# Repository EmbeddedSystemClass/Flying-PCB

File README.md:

# Infineon's full system solution for multicopter

Multicopter project by Management Center Innsbruck and Infineon Technologies Austria AG.

The here present project deals with the development of a radio-controlled quadcopter and focusses on two major topics:

- Design and implementation of an appropriate digital attitude controller/flightcontroller (named LARIX Flight Controller)
- Development of a brushless DC (BLDC) motor controller (named PINUS Electronic Speed Controller)

More information Infineon and Multicopters: http://www.infineon.com/multicopter

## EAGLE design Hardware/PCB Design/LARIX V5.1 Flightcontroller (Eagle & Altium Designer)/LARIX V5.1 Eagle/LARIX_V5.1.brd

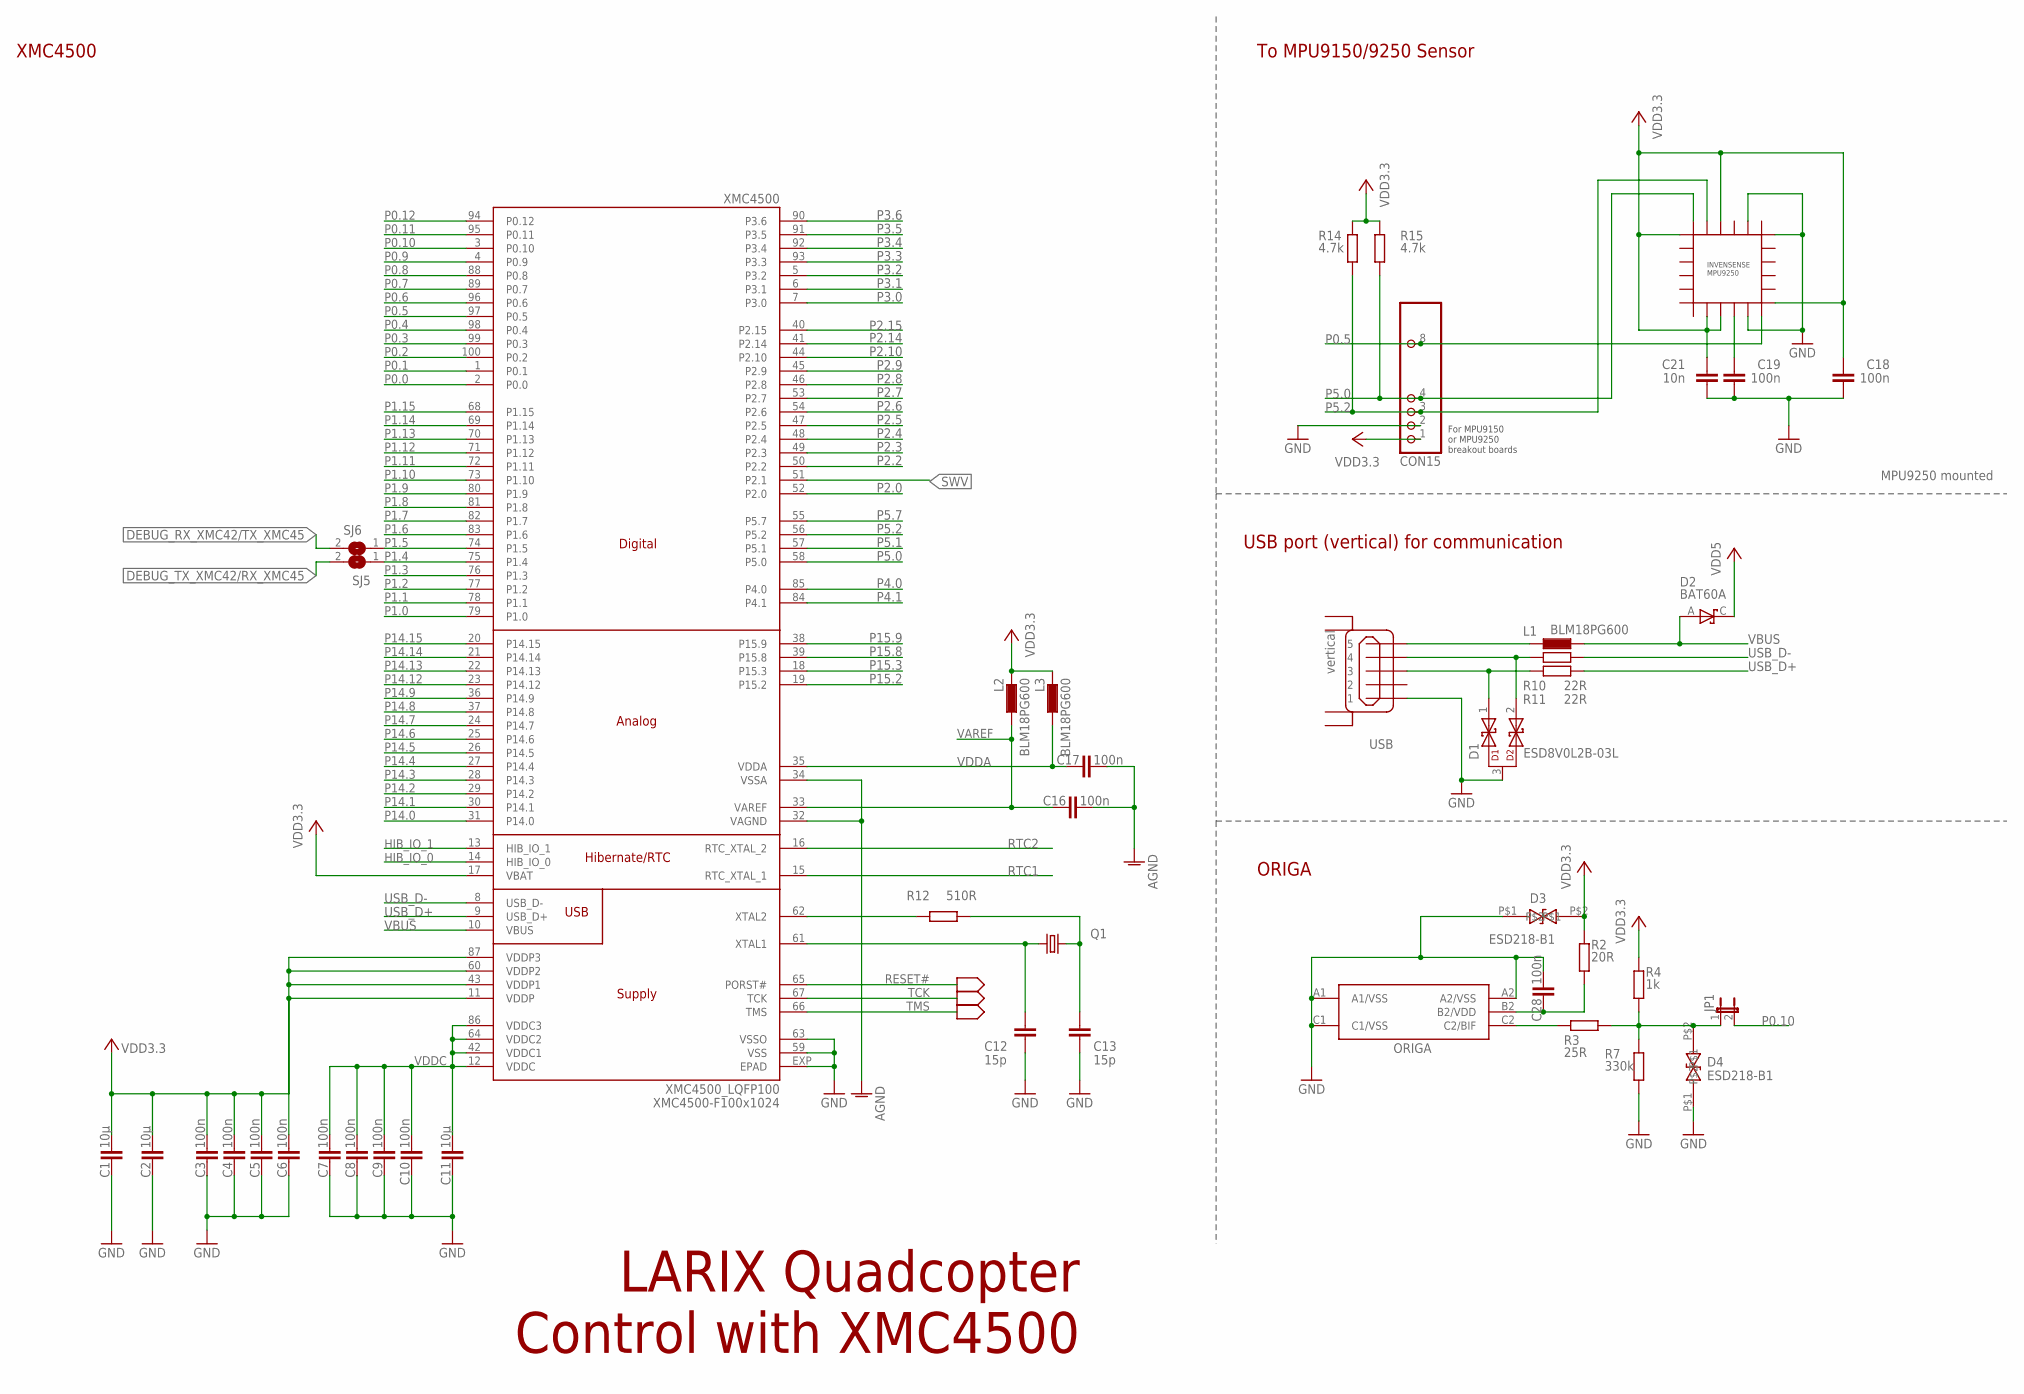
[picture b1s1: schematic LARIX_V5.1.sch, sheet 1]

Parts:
C1, C2, C11: 10µ; C0805K
C3, C4, C5, C6, C7, C8, C9, C10, C16, C17, C18, C19, C28: 100n; C0603
C12, C13: 15p; C0603
C21: 10n; C0603
CON15: PINHD-1X10; 1X10
D1: ESD8V0L2B-03L; TSLP-3-1
D2: BAT60A; SOD323-R
D3, D4: ESD218-B1-02EL; TSLP-2-20
JP1: JP1E; JP1
L1, L2, L3: BLM18PG600; L1608
MPU9250: MPU9250; QFN3X3-24+
ORIGA: ORIGA2L; WLB-5
Q1: 12MHZ/S/3.2X2.5; 32X25_4PAD
R2: 20R; R0603
R3: 25R; R0603
R4: 1k; R0603
R7: 330k; R0603
R10, R11: 22R; R0603
R12: 510R; R0603
R14, R15: 4.7k; R0603
SJ5, SJ6: SJ
USB: vertical; USBVERTICAL
XMC4500: XMC4500_LQFP100; P/PG-LQFP-100-11

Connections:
AGND: C16.2, C17.2, XMC4500.32 (VAGND), XMC4500.34 (VSSA)
DEBUG_RX_XMC42/TX_XMC45: SJ6.2; also elsewhere on the board
DEBUG_TX_XMC42/RX_XMC45: SJ5.2; also elsewhere on the board
GND: C1.2, C2.2, C3.2, C4.2, C5.2, C6.2, C7.2, C8.2, C9.2, C10.2, C11.2, C12.2, C13.2, C18.1, C19.1, C21.1, C28.1, CON15.2, D1.3, D3.P$1, D4.P$1, MPU9250.11, MPU9250.18, MPU9250.20, ORIGA.A1 (A1/VSS), ORIGA.A2 (A2/VSS), ORIGA.C1 (C1/VSS), R7.2, USB.1, XMC4500.59 (VSS), XMC4500.63 (VSSO), XMC4500.EXP (EPAD); also elsewhere on the board
HIB_IO_0: XMC4500.14 (HIB_IO_0)
HIB_IO_1: XMC4500.13 (HIB_IO_1)
unnamed: C28.2, ORIGA.B2 (B2/VDD), R2.2
unnamed: R12.1, XMC4500.62 (XTAL2)
unnamed: C13.1, Q1.3 (2), R12.2
unnamed: C12.1, Q1.1, XMC4500.61 (XTAL1)
unnamed: D4.P$2, JP1.1, R3.2, R4.2, R7.1
unnamed: L1.2, USB.5
unnamed: ORIGA.C2 (C2/BIF), R3.1
unnamed: D1.2, R10.1, USB.4
unnamed: C19.2, MPU9250.10
unnamed: D1.1, R11.1, USB.3+ (3)
P0.0: XMC4500.2 (P0.0); also elsewhere on the board
P0.1: XMC4500.1 (P0.1); also elsewhere on the board
P0.2: XMC4500.100 (P0.2); also elsewhere on the board
P0.3: XMC4500.99 (P0.3); also elsewhere on the board
P0.4: XMC4500.98 (P0.4); also elsewhere on the board
P0.5: CON15.8, MPU9250.12, XMC4500.97 (P0.5)
P0.6: XMC4500.96 (P0.6)
P0.7: XMC4500.89 (P0.7); also elsewhere on the board
P0.8: XMC4500.88 (P0.8)
P0.9: XMC4500.4 (P0.9); also elsewhere on the board
P0.10: JP1.2, XMC4500.3 (P0.10)
P0.11: XMC4500.95 (P0.11)
P0.12: XMC4500.94 (P0.12)
P1.0: XMC4500.79 (P1.0); also elsewhere on the board
P1.1: XMC4500.78 (P1.1); also elsewhere on the board
P1.2: XMC4500.77 (P1.2); also elsewhere on the board
P1.3: XMC4500.76 (P1.3); also elsewhere on the board
P1.4: SJ5.1, XMC4500.75 (P1.4)
P1.5: SJ6.1, XMC4500.74 (P1.5); also elsewhere on the board
P1.6: XMC4500.83 (P1.6)
P1.7: XMC4500.82 (P1.7)
P1.8: XMC4500.81 (P1.8)
P1.9: XMC4500.80 (P1.9)
P1.10: XMC4500.73 (P1.10)
P1.11: XMC4500.72 (P1.11)
P1.12: XMC4500.71 (P1.12)
P1.13: XMC4500.70 (P1.13)
P1.14: XMC4500.69 (P1.14)
P1.15: XMC4500.68 (P1.15); also elsewhere on the board
P2.0: XMC4500.52 (P2.0)
P2.2: XMC4500.50 (P2.2); also elsewhere on the board
P2.3: XMC4500.49 (P2.3); also elsewhere on the board
P2.4: XMC4500.48 (P2.4); also elsewhere on the board
P2.5: XMC4500.47 (P2.5); also elsewhere on the board
P2.6: XMC4500.54 (P2.6)
P2.7: XMC4500.53 (P2.7)
P2.8: XMC4500.46 (P2.8)
P2.9: XMC4500.45 (P2.9)
P2.10: XMC4500.44 (P2.10)
P2.14: XMC4500.41 (P2.14)
P2.15: XMC4500.40 (P2.15)
P3.0: XMC4500.7 (P3.0); also elsewhere on the board
P3.1: XMC4500.6 (P3.1); also elsewhere on the board
P3.2: XMC4500.5 (P3.2); also elsewhere on the board
P3.3: XMC4500.93 (P3.3)
P3.4: XMC4500.92 (P3.4)
P3.5: XMC4500.91 (P3.5); also elsewhere on the board
P3.6: XMC4500.90 (P3.6)
P4.0: XMC4500.85 (P4.0); also elsewhere on the board
P4.1: XMC4500.84 (P4.1)
P5.0: CON15.4, MPU9250.24, R15.1, XMC4500.58 (P5.0)
P5.1: XMC4500.57 (P5.1); also elsewhere on the board
P5.2: CON15.3, MPU9250.23, R14.1, XMC4500.56 (P5.2)
P5.7: XMC4500.55 (P5.7)
P14.0: XMC4500.31 (P14.0)
P14.1: XMC4500.30 (P14.1)
P14.2: XMC4500.29 (P14.2)
P14.3: XMC4500.28 (P14.3)
P14.4: XMC4500.27 (P14.4)
P14.5: XMC4500.26 (P14.5); also elsewhere on the board
P14.6: XMC4500.25 (P14.6)
P14.7: XMC4500.24 (P14.7); also elsewhere on the board
P14.8: XMC4500.37 (P14.8); also elsewhere on the board
P14.9: XMC4500.36 (P14.9)
P14.12: XMC4500.23 (P14.12)
P14.13: XMC4500.22 (P14.13)
P14.14: XMC4500.21 (P14.14)
P14.15: XMC4500.20 (P14.15)
P15.2: XMC4500.19 (P15.2)
P15.3: XMC4500.18 (P15.3)
P15.8: XMC4500.39 (P15.8)
P15.9: XMC4500.38 (P15.9)
RESET#: XMC4500.65 (PORST#); also elsewhere on the board
RTC1: XMC4500.15 (RTC_XTAL_1)
RTC2: XMC4500.16 (RTC_XTAL_2)
SWV: XMC4500.51 (P2.1); also elsewhere on the board
TCK: XMC4500.67 (TCK); also elsewhere on the board
TMS: XMC4500.66 (TMS); also elsewhere on the board
USB_D+: R11.2, XMC4500.9 (USB_D+)
USB_D-: R10.2, XMC4500.8 (USB_D-)
VAREF: C16.1, L2.1, XMC4500.33 (VAREF)
VBUS: D2.A, L1.1, XMC4500.10 (VBUS)
VDD3.3: C1.1, C2.1, C3.1, C4.1, C5.1, C6.1, C18.2, C21.2, CON15.1, D3.P$2, L2.2, L3.2, MPU9250.1, MPU9250.8, MPU9250.9, MPU9250.13, MPU9250.22, R2.1, R4.1, R14.2, R15.2, XMC4500.11 (VDDP), XMC4500.17 (VBAT), XMC4500.43 (VDDP1), XMC4500.60 (VDDP2), XMC4500.87 (VDDP3); also elsewhere on the board
VDD5: D2.C; also elsewhere on the board
VDDA: C17.1, L3.1, XMC4500.35 (VDDA)
VDDC: C7.1, C8.1, C9.1, C10.1, C11.1, XMC4500.12 (VDDC), XMC4500.42 (VDDC1), XMC4500.64 (VDDC2), XMC4500.86 (VDDC3)

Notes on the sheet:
LARIX Quadcopter Control with XMC4500
XMC4500-F100x1024
To MPU9150/9250 Sensor
ORIGA
XMC4500
For MPU9150 or MPU9250 breakout boards
USB port (vertical) for communication
ESD218-B1
MPU9250 mounted

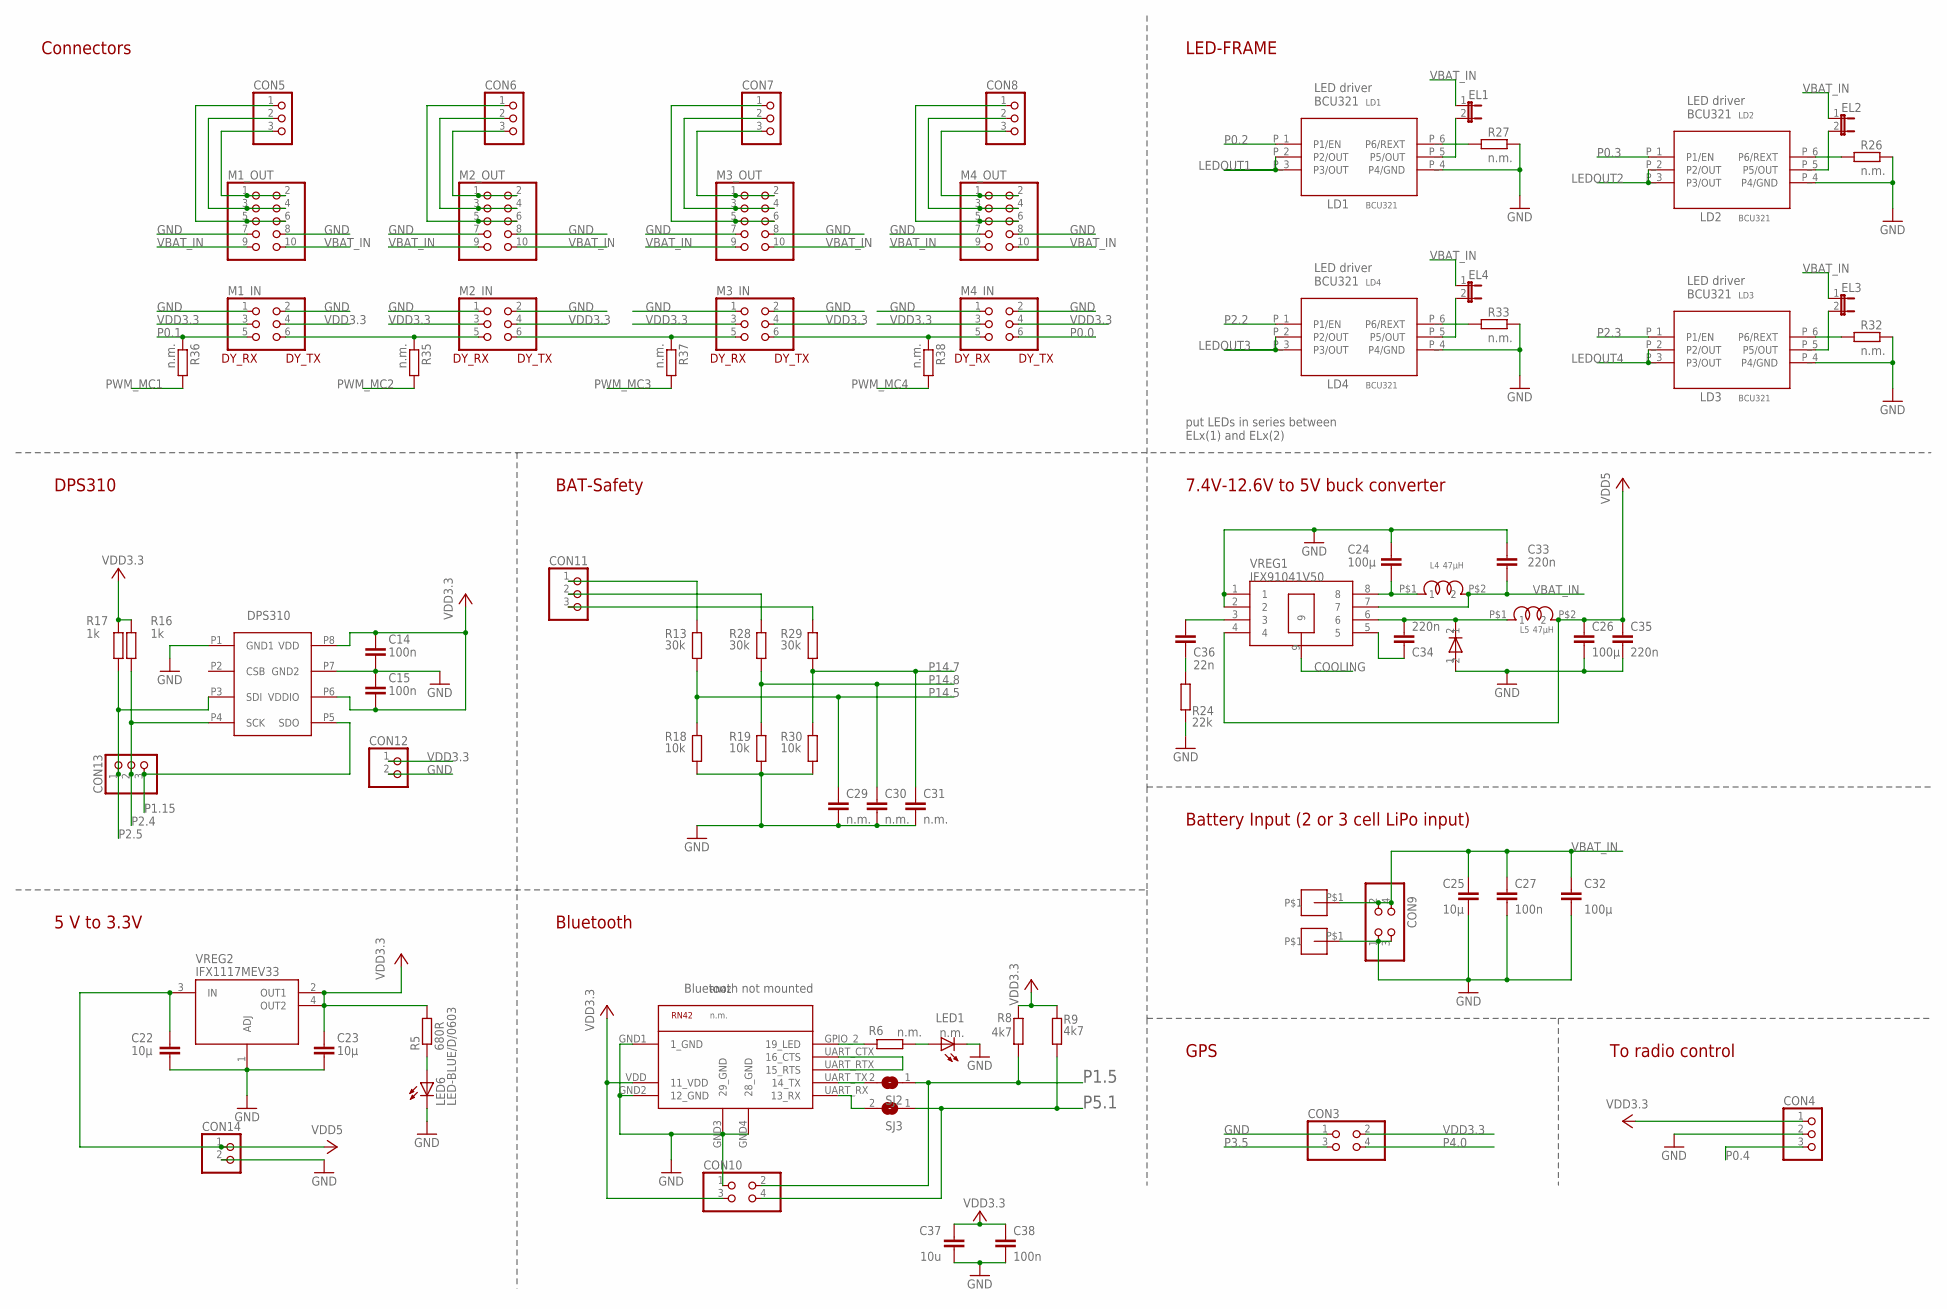
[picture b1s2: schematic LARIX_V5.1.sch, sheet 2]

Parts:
C14, C15, C27, C38: 100n; C0603
C22, C23, C25: 10µ; C0805K
C24, C26, C32: 100µ; C1210
C29, C30, C31: n.m.; C0603
C33, C34, C35: 220n; C0603
C36: 22n; C0603
C37: 10u; C0805K
CON3, CON9, CON10: PINHD-2X2; 2X02
CON4, CON5, CON6, CON7, CON8, CON11, CON13: PINHD-1X3; 1X03
CON12, CON14: PINHD-1X2; 1X02
D6: BAS21-03W; INF-SOD323_V_1PRIMARY
DPS310: Infineon; LGA8R125P0X4_500X300X120
EL1, EL2, EL3, EL4: JP1E; JP1
L4, L5: 47µH; WE-TPC
LD1, LD2, LD3, LD4: BCU321; SC74
LED1: n.m.; CHIPLED_0603
LED6: LED-BLUE/D/0603; CHIPLED_0603
M1_IN, M2_IN, M3_IN, M4_IN: PINHD-2X3; 2X03
M1_OUT, M2_OUT, M3_OUT, M4_OUT: PINHD-2X5; 2X05
PAD1, PAD2: PAD-BATTERY; BATT-SOLDER
R5: 680R; R0603
R6, R26, R27, R32, R33, R35, R36, R37, R38: n.m.; R0603
R8, R9: 4k7; R0603
R13, R28, R29: 30k; R0603
R16, R17: 1k; R0603
R18, R19, R30: 10k; R0603
R24: 22k; R0603
RN42: n.m.; RN42+SHIELD
SJ2, SJ3: SJ
VREG1: IFX91041V50; INF-PG-DSO-8-27_N_1PRIMARY
VREG2: IFX1117MEV33; SOT223

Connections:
COOLING: VREG1.9
GND: C14.2, C15.1, C22.2, C23.2, C24.1, C25.2, C26.2, C27.2, C29.2, C30.2, C31.2, C32.2, C33.1, C35.2, C37.2, C38.2, CON3.1, CON4.2, CON9.1, CON9.3, CON10.1, CON12.2, CON14.2, D6.1, DPS310.P1 (GND1), DPS310.P7 (GND2), LD1.P_4 (P4/GND), LD2.P_4 (P4/GND), LD3.P_4 (P4/GND), LD4.P_4 (P4/GND), LED1.C, LED6.C, M1_IN.1, M1_IN.2, M1_OUT.7, M1_OUT.8, M2_IN.1, M2_IN.2, M2_OUT.7, M2_OUT.8, M3_IN.1, M3_IN.2, M3_OUT.7, M3_OUT.8, M4_IN.1, M4_IN.2, M4_OUT.7, M4_OUT.8, PAD2.P$1, R18.2, R19.2, R24.2, R26.2, R27.2, R30.2, R32.2, R33.2, RN42.GND1 (1_GND), RN42.GND2 (12_GND), RN42.GND3 (29_GND), RN42.GND4 (28_GND), VREG1.1, VREG1.2, VREG2.1 (ADJ); also elsewhere on the board
LEDOUT1: EL1.2, LD1.P_2 (P2/OUT), LD1.P_3 (P3/OUT), LD1.P_5 (P5/OUT)
LEDOUT2: EL2.2, LD2.P_2 (P2/OUT), LD2.P_3 (P3/OUT), LD2.P_5 (P5/OUT)
LEDOUT3: EL4.2, LD4.P_2 (P2/OUT), LD4.P_3 (P3/OUT), LD4.P_5 (P5/OUT)
LEDOUT4: EL3.2, LD3.P_2 (P2/OUT), LD3.P_3 (P3/OUT), LD3.P_5 (P5/OUT)
unnamed: C36.1, VREG1.3
unnamed: CON5.1, M1_OUT.5, M1_OUT.6
unnamed: LED6.A, R5.1
unnamed: M2_IN.6, M3_IN.5, R37.1
unnamed: C36.2, R24.1
unnamed: LED1.A, R6.1
unnamed: CON5.2, M1_OUT.3, M1_OUT.4
unnamed: CON5.3, M1_OUT.1, M1_OUT.2
unnamed: R6.2, RN42.GPIO_2 (19_LED)
unnamed: RN42.UART_CTX (16_CTS), RN42.UART_RTX (15_RTS)
unnamed: C24.2, L4.P$1 (1), VREG1.8
unnamed: C34.1, D6.2, L5.P$1 (1), VREG1.6
unnamed: LD2.P_6 (P6/REXT), R26.1
unnamed: LD1.P_6 (P6/REXT), R27.1
unnamed: CON6.1, M2_OUT.5, M2_OUT.6
unnamed: CON11.1, R13.1
unnamed: CON6.3, M2_OUT.1, M2_OUT.2
unnamed: CON6.2, M2_OUT.3, M2_OUT.4
unnamed: CON11.2, R28.1
unnamed: CON8.1, M4_OUT.5, M4_OUT.6
unnamed: CON11.3, R29.1
unnamed: CON8.3, M4_OUT.1, M4_OUT.2
unnamed: CON8.2, M4_OUT.3, M4_OUT.4
unnamed: C34.2, VREG1.5
unnamed: CON7.1, M3_OUT.5, M3_OUT.6
unnamed: CON7.2, M3_OUT.3, M3_OUT.4
unnamed: CON7.3, M3_OUT.1, M3_OUT.2
unnamed: M3_IN.6, M4_IN.5, R38.1
unnamed: M1_IN.6, M2_IN.5, R35.1
unnamed: LD3.P_6 (P6/REXT), R32.1
unnamed: LD4.P_6 (P6/REXT), R33.1
unnamed: RN42.UART_TX (14_TX), SJ2.2
unnamed: RN42.UART_RX (13_RX), SJ3.2
P0.0: M4_IN.6; also elsewhere on the board
P0.1: M1_IN.5, R36.1; also elsewhere on the board
P0.2: LD1.P_1 (P1/EN); also elsewhere on the board
P0.3: LD2.P_1 (P1/EN); also elsewhere on the board
P0.4: CON4.3; also elsewhere on the board
P1.5: CON10.2, R8.2, SJ2.1; also elsewhere on the board
P1.15: CON13.3, DPS310.P5 (SDO); also elsewhere on the board
P2.2: LD4.P_1 (P1/EN); also elsewhere on the board
P2.3: LD3.P_1 (P1/EN); also elsewhere on the board
P2.4: CON13.2, DPS310.P4 (SCK), R16.2; also elsewhere on the board
P2.5: CON13.1, DPS310.P3 (SDI), R17.2; also elsewhere on the board
P3.5: CON3.3; also elsewhere on the board
P4.0: CON3.4; also elsewhere on the board
P5.1: CON10.4, R9.2, SJ3.1; also elsewhere on the board
P14.5: C29.1, R13.2, R18.1; also elsewhere on the board
P14.7: C31.1, R29.2, R30.1; also elsewhere on the board
P14.8: C30.1, R19.1, R28.2; also elsewhere on the board
PWM_MC1: R36.2; also elsewhere on the board
PWM_MC2: R35.2; also elsewhere on the board
PWM_MC3: R37.2; also elsewhere on the board
PWM_MC4: R38.2; also elsewhere on the board
VBAT_IN: C25.1, C27.1, C32.1, C33.2, CON9.2, CON9.4, EL1.1, EL2.1, EL3.1, EL4.1, L4.P$2 (2), M1_OUT.9, M1_OUT.10, M2_OUT.9, M2_OUT.10, M3_OUT.9, M3_OUT.10, M4_OUT.9, M4_OUT.10, PAD1.P$1, VREG1.7
VDD3.3: C14.1, C15.2, C23.1, C37.1, C38.1, CON3.2, CON4.1, CON10.3, CON12.1, DPS310.P6 (VDDIO), DPS310.P8 (VDD), M1_IN.3, M1_IN.4, M2_IN.3, M2_IN.4, M3_IN.3, M3_IN.4, M4_IN.3, M4_IN.4, R5.2, R8.1, R9.1, R16.1, R17.1, RN42.VDD (11_VDD), VREG2.2 (OUT1), VREG2.4 (OUT2); also elsewhere on the board
VDD5: C22.1, C26.1, C35.1, CON14.1, L5.P$2 (2), VREG1.4, VREG2.3 (IN); also elsewhere on the board

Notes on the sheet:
Connectors
DY_RX
DY_TX
LED-FRAME
LED driver BCU321
LD1
LD2
LD4
LD3
GPS
To radio control
DPS310
5 V to 3.3V
7.4V-12.6V to 5V buck converter
Bluetooth
BAT-Safety
Battery Input (2 or 3 cell LiPo input)
VREG1 IFX91041V50
Bluetooth not mounted
put LEDs in series between ELx(1) and ELx(2)

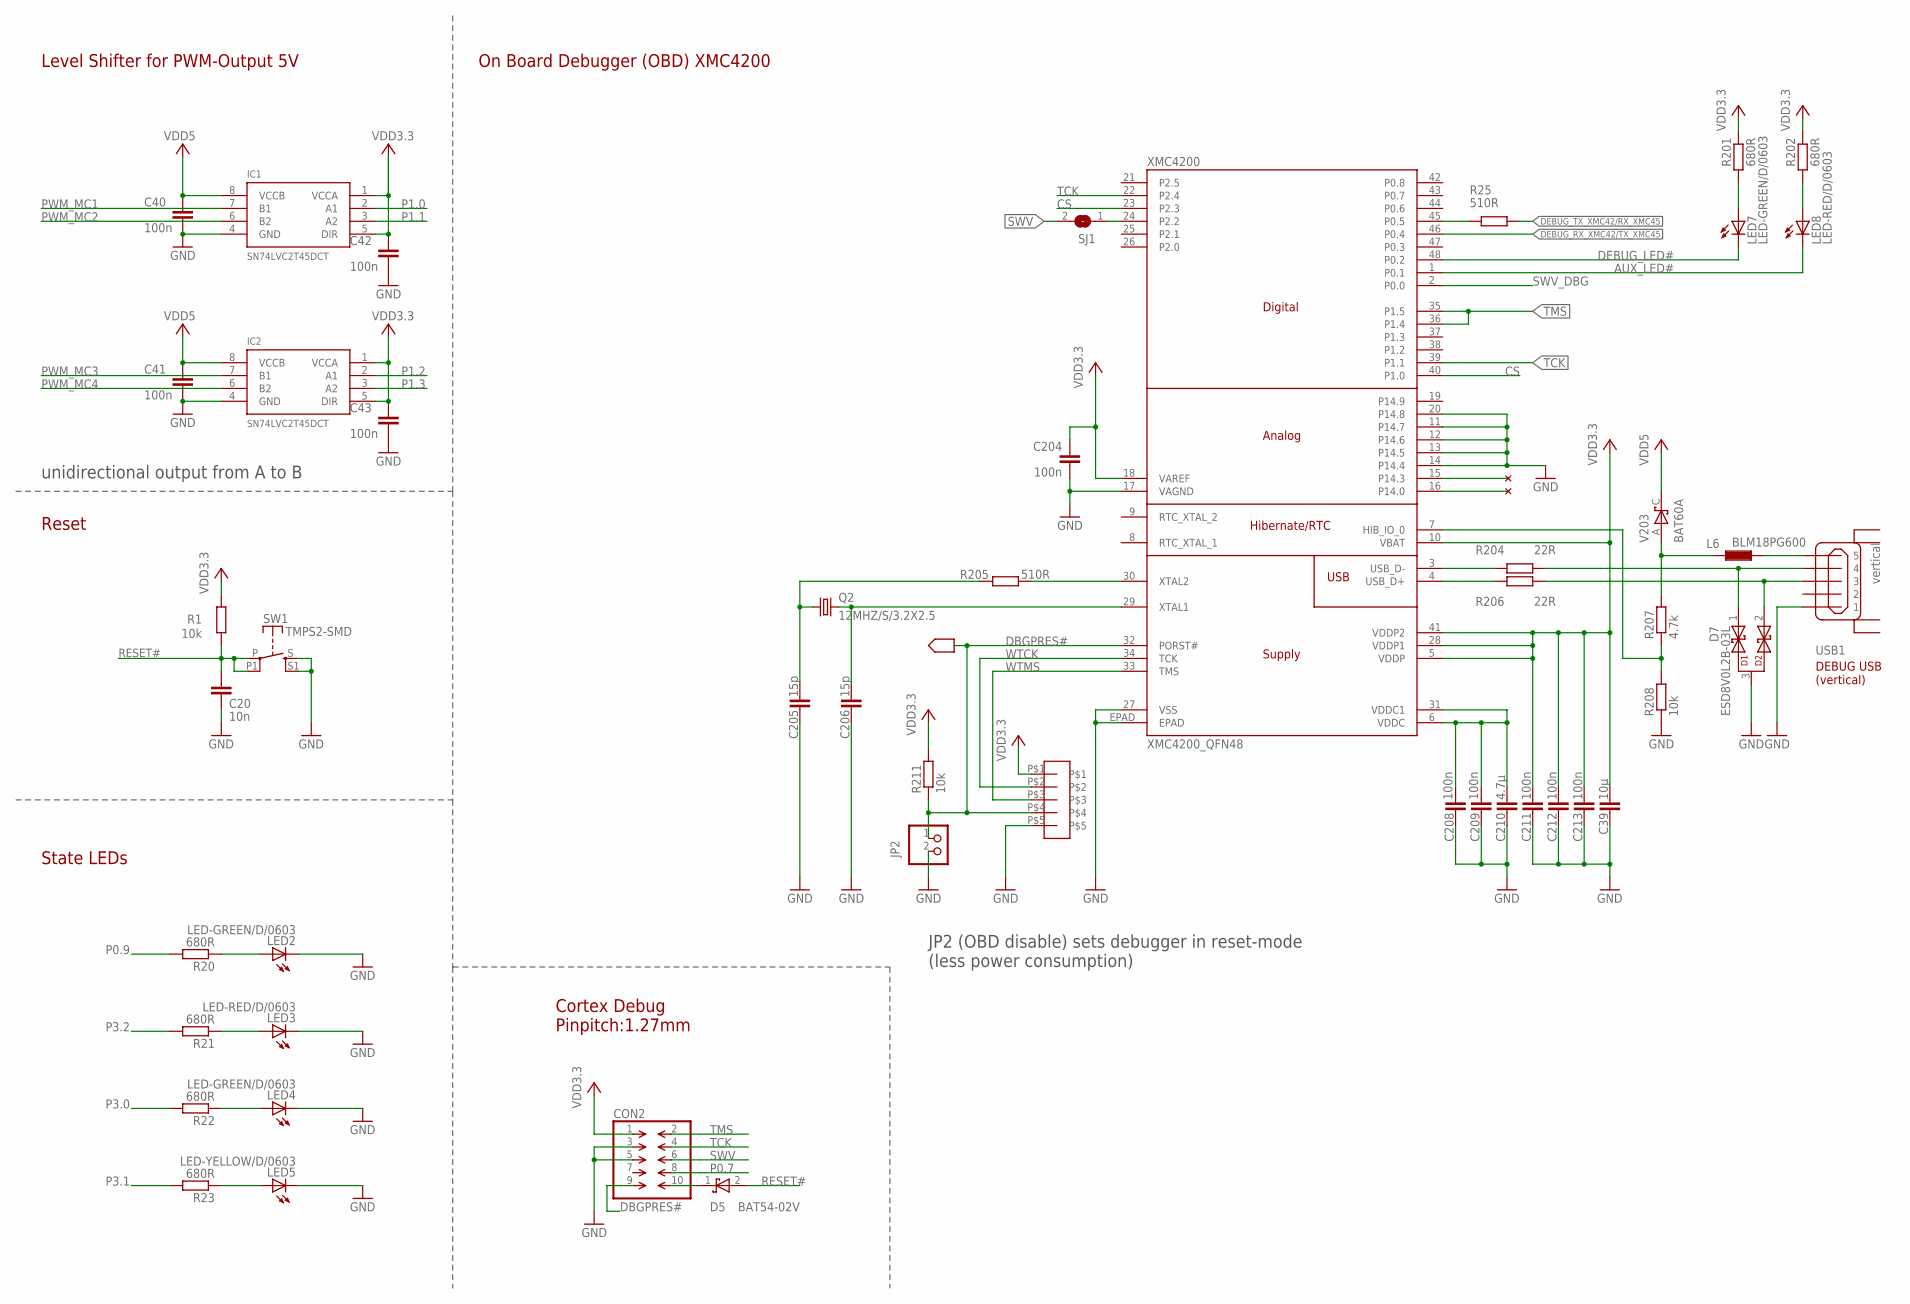
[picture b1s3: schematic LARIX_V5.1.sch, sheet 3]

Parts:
C20: 10n; C0603
C39: 10µ; C0805K
C40, C41, C42, C43: 100n; C0603
C204, C208, C209, C211, C212, C213: 100n; C0402
C205, C206: 15p; C0402
C210: 4.7µ; C0805K
CON2: FTSH-105-01-F-D-K
D5: BAT54-02V; SC79
D7: ESD8V0L2B-03L; TSLP-3-1
IC1, IC2: SN74LVC2T45DCT; DCT_R-PDSO-G8
JP2: PINHD-1X2; 1X02
L6: BLM18PG600; L1608
LED2, LED4, LED7: LED-GREEN/D/0603; CHIPLED_0603
LED3, LED8: LED-RED/D/0603; CHIPLED_0603
LED5: LED-YELLOW/D/0603; CHIPLED_0603
Q2: 12MHZ/S/3.2X2.5; 32X25_4PAD
R1: 10k; R0603
R20, R21, R22, R23, R201, R202: 680R; R0603
R25: 510R; R0402
R204, R206: 22R; R0402
R205: 510R; R0603
R207: 4.7k; R0402
R208, R211: 10k; R0402
SJ1: SJ
SW1: TMPS2-SMD; FSM2JSMA
U$9: 127MARKED; PINHEAD_127
U$11: SEGGER.L_100; LOGO_100
USB1: vertical; USBVERTICAL
V203: BAT60A; SOD323-R
XMC4200: XMC4200_QFN48; QFN-48-7X7

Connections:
AUX_LED#: LED8.C, XMC4200.1 (P0.1)
CS: XMC4200.23 (P2.3), XMC4200.40 (P1.0)
DBGPRES#: CON2.9, JP2.1, R211.1, U$9.P$4, XMC4200.32 (PORST#)
DEBUG_LED#: LED7.C, XMC4200.48 (P0.2)
DEBUG_RX_XMC42/TX_XMC45: XMC4200.46 (P0.4); also elsewhere on the board
DEBUG_TX_XMC42/RX_XMC45: R25.2; also elsewhere on the board
GND: C20.2, C39.2, C40.2, C41.2, C42.2, C43.2, C204.2, C205.2, C206.2, C208.2, C209.2, C210.2, C211.2, C212.2, C213.2, CON2.3, CON2.5, D7.3, IC1.4 (GND), IC2.4 (GND), JP2.2, LED2.C, LED3.C, LED4.C, LED5.C, R208.1, SW1.S, SW1.S1 (S), U$9.P$5, USB1.1, XMC4200.11 (P14.7), XMC4200.12 (P14.6), XMC4200.13 (P14.5), XMC4200.14 (P14.4), XMC4200.17 (VAGND), XMC4200.20 (P14.8), XMC4200.27 (VSS), XMC4200.EPAD; also elsewhere on the board
unnamed: LED2.A, R20.1
unnamed: LED3.A, R21.1
unnamed: D7.1, R204.2, USB1.4
unnamed: CON2.10, D5.1 (C)
unnamed: LED4.A, R22.1
unnamed: LED5.A, R23.1
unnamed: D7.2, R206.2, USB1.3+ (3)
unnamed: C205.1, Q2.1, R205.2
unnamed: R205.1, XMC4200.30 (XTAL2)
unnamed: L6.2, R207.2, V203.A
unnamed: C206.1, Q2.3 (2), XMC4200.29 (XTAL1)
unnamed: LED7.A, R201.2
unnamed: R25.1, XMC4200.45 (P0.5)
unnamed: R207.1, R208.2, XMC4200.7 (HIB_IO_0)
unnamed: LED8.A, R202.2
P0.7: CON2.8; also elsewhere on the board
P0.9: R20.2; also elsewhere on the board
P1.0: IC1.2 (A1); also elsewhere on the board
P1.1: IC1.3 (A2); also elsewhere on the board
P1.2: IC2.2 (A1); also elsewhere on the board
P1.3: IC2.3 (A2); also elsewhere on the board
P3.0: R22.2; also elsewhere on the board
P3.1: R23.2; also elsewhere on the board
P3.2: R21.2; also elsewhere on the board
PWM_MC1: IC1.7 (B1); also elsewhere on the board
PWM_MC2: IC1.6 (B2); also elsewhere on the board
PWM_MC3: IC2.7 (B1); also elsewhere on the board
PWM_MC4: IC2.6 (B2); also elsewhere on the board
RESET#: C20.1, D5.2 (A), R1.1, SW1.P, SW1.P1; also elsewhere on the board
SWV: CON2.6, SJ1.2; also elsewhere on the board
SWV_DBG: SJ1.1, XMC4200.2 (P0.0), XMC4200.24 (P2.2)
TCK: CON2.4, XMC4200.22 (P2.4), XMC4200.39 (P1.1); also elsewhere on the board
TMS: CON2.2, XMC4200.35 (P1.5), XMC4200.36 (P1.4); also elsewhere on the board
USBVCC: L6.1, USB1.5
VDD3.3: C39.1, C42.1, C43.1, C204.1, C211.1, C212.1, C213.1, CON2.1, IC1.1 (VCCA), IC1.5 (DIR), IC2.1 (VCCA), IC2.5 (DIR), R1.2, R201.1, R202.1, R211.2, U$9.P$1, XMC4200.5 (VDDP), XMC4200.10 (VBAT), XMC4200.18 (VAREF), XMC4200.28 (VDDP1), XMC4200.41 (VDDP2); also elsewhere on the board
VDD5: C40.1, C41.1, IC1.8 (VCCB), IC2.8 (VCCB), V203.C; also elsewhere on the board
WTCK: U$9.P$2, XMC4200.34 (TCK)
WTMS: U$9.P$3, XMC4200.33 (TMS)
WUSB_DM: R204.1, XMC4200.3 (USB_D-)
WUSB_DP: R206.1, XMC4200.4 (USB_D+)
WVDDC: C208.1, C209.1, C210.1, XMC4200.6 (VDDC), XMC4200.31 (VDDC1)

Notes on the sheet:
State LEDs
Reset
Level Shifter for PWM-Output 5V
DEBUG USB (vertical)
Cortex Debug Pinpitch:1.27mm
On Board Debugger (OBD) XMC4200
JP2 (OBD disable) sets debugger in reset-mode (less power consumption)
unidirectional output from A to B

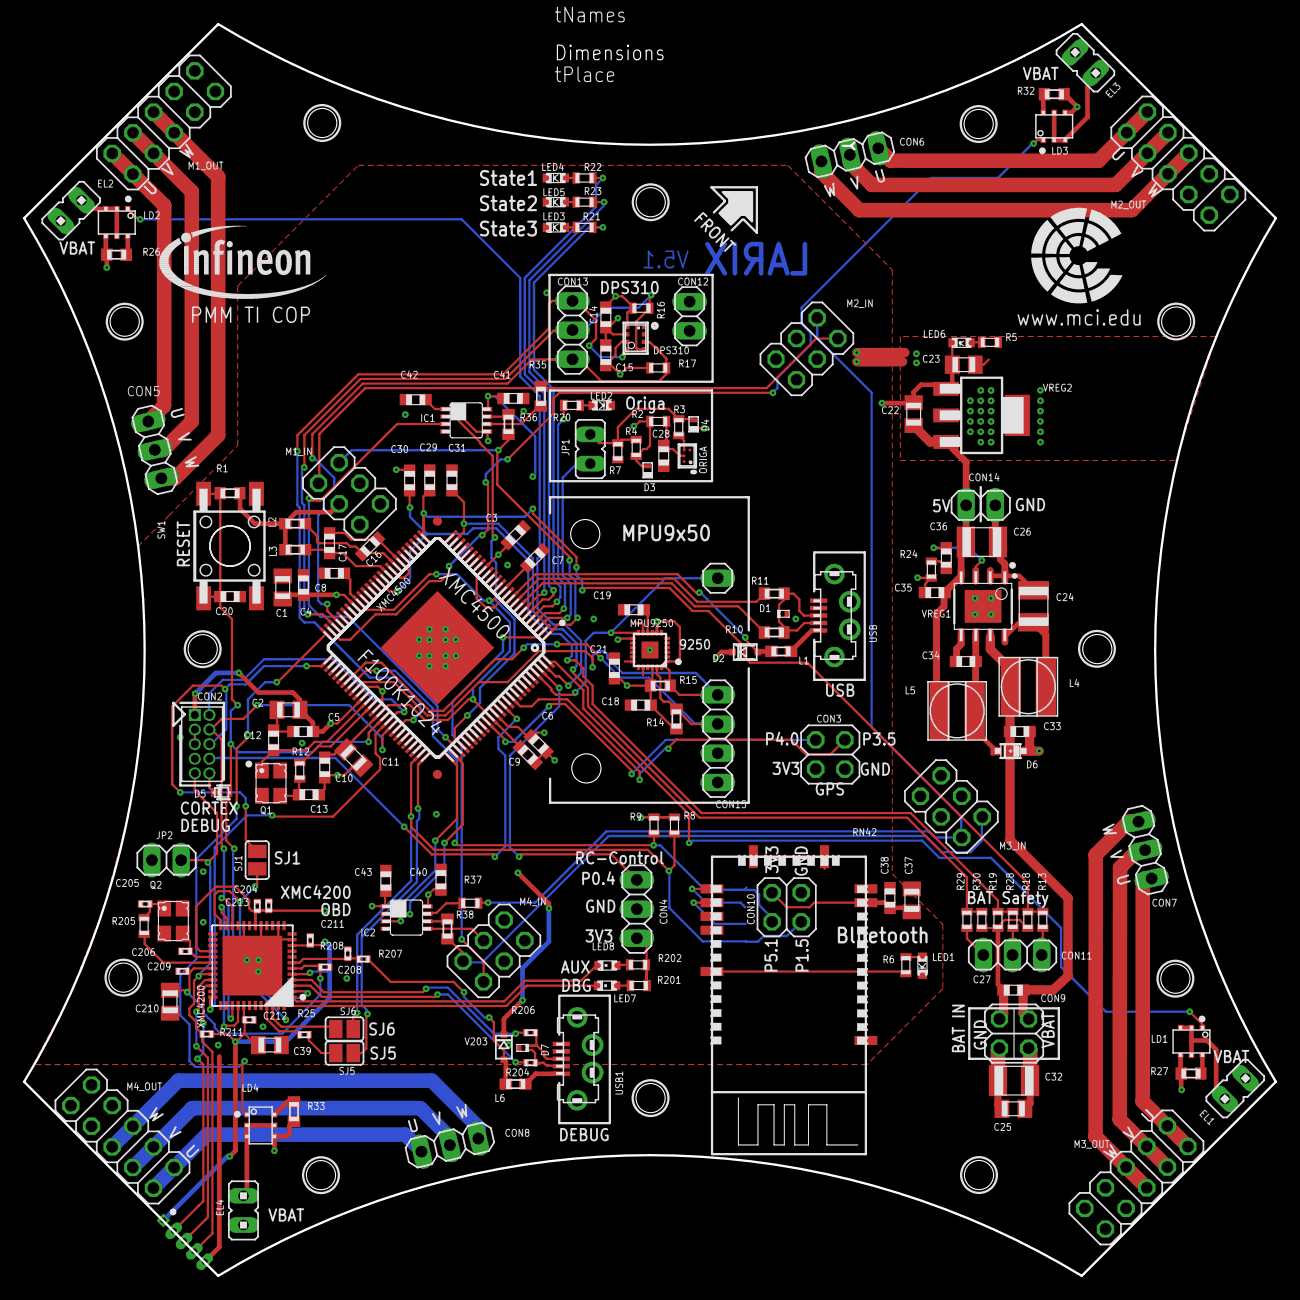
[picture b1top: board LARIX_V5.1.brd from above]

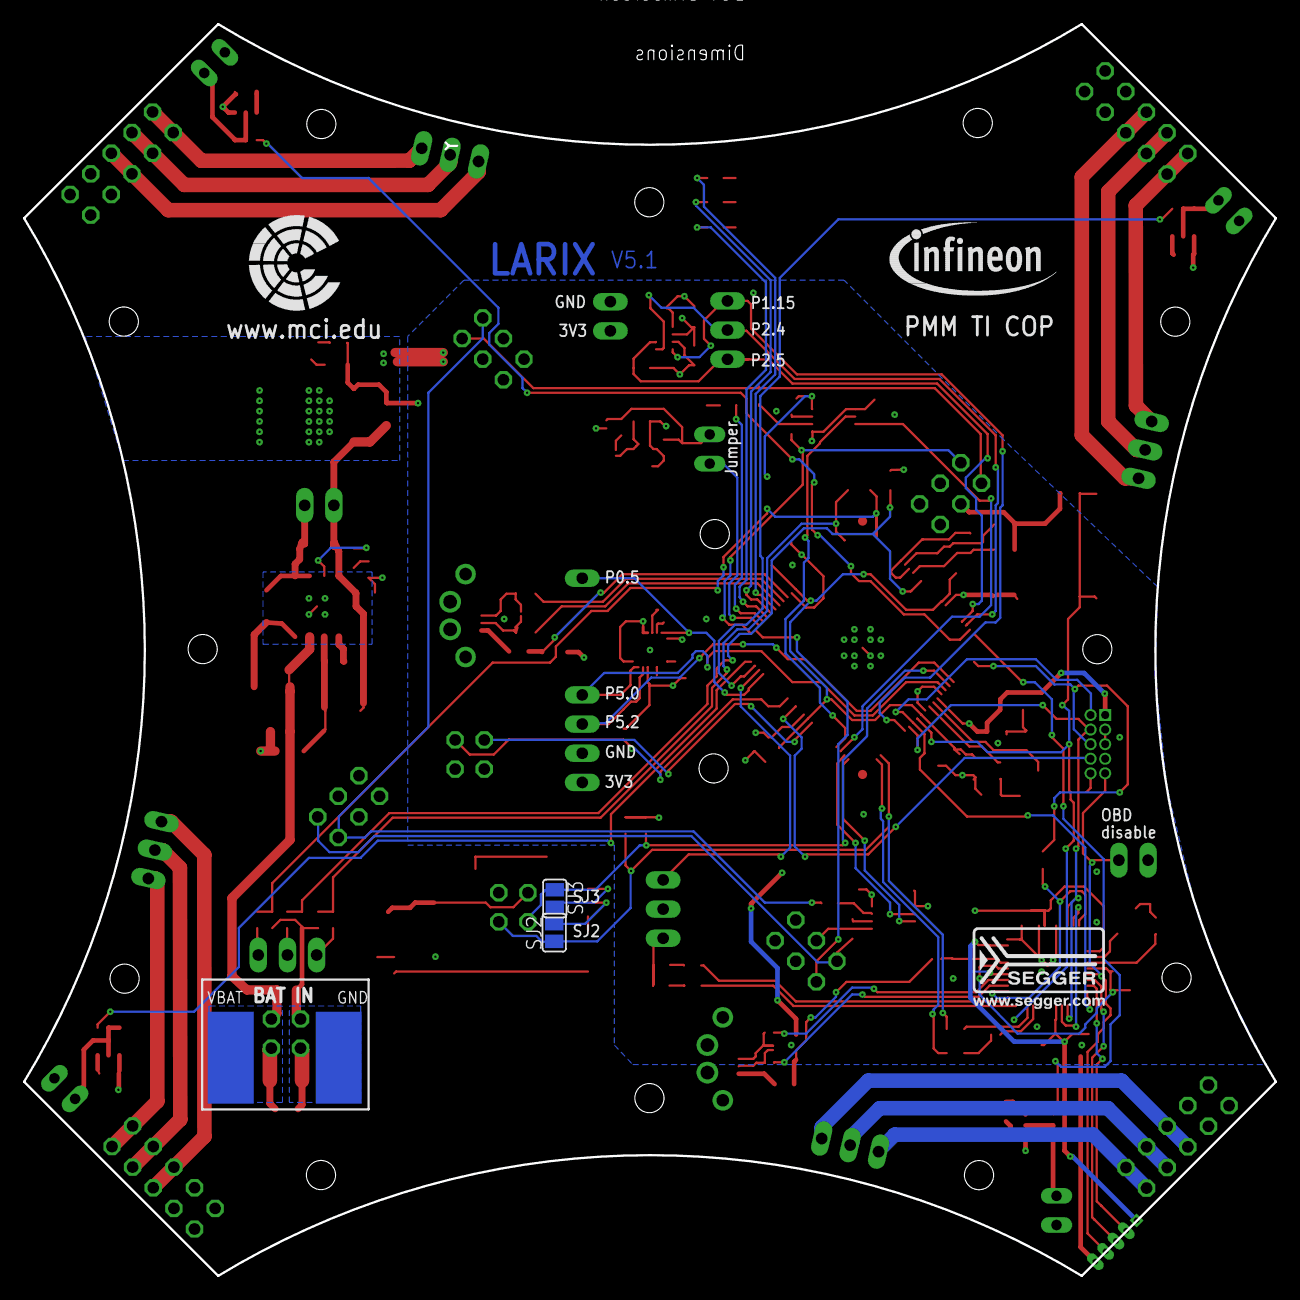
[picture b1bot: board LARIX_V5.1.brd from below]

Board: 4 copper layers, 109.0 x 109.0 mm, 174 parts (4 on the bottom side), 125 nets.

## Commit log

2016-07-13 Updated folder structure
    - Updated the software to the latest versions
    - added LARIX Android Control Software
2016-07-13 Added flightframe pictures
2016-07-13 Corrected some errors
2016-07-14 removed copter.rocks data
    removed all Widefield related stuff Software/Hardware and moved to a new
    repository "copter.rocks"
2016-07-14 unzipped LARIX Android Control
    unzipped file and deleted zip
2016-07-14 removed Simulations folder
    the Simulations
2016-07-26 New ESC-Software
    Added new ESC-Software
2016-07-28 Test
    Test
2016-08-02 Deleted unnecessary files
2016-08-04 Changed updaterate of Bluetooth-Connection in Android App
    Changed updaterate bluetooth connection in android app. Is now about
    25Hz.
2016-08-12 Create .gitignore.
2016-08-12 Uncomment "#define BT_ONLY" and add a function declaration.
    Uncomment "#define BT_ONLY" to enable app input without connecting UART RC.
    Add function declaration of Blouetooth_Keep_Alive() to solve the problem of unstable BT connection.
2016-08-13 Realize the calculation of altitude.
    A new interrupt app(NVIC002/12[FY_Alt_Ctrl]) is created for altitude control, corresponding interrupt handler:(Alt_Controller_Int_Handler,priority=20).
    It is triggered by a new PWM Timer(PWMSP001/4[FY_AltCtrl_Timer]) with a frequency of 10Hz.
    Notice: must run 'DAVE -- Generate Code' after creating or changing apps, or it will not work!!!!
    Further development will be done in _Quadrocopter/Dev folder.
2016-08-13 Update all generated file.
    My personal code path is different from origin version, so the DAVE IDE changed a lot of stuffs, including newline(lf->crlf).
    This should not be big deal. As long as the source code is correct, I expect 'DAVE -- Generate Code' shoule work under different circumstances.
2016-08-14 Figure out the coordinate systems of accel/gyro/mag and their transformation.
    According to datasheet, coordinates on chip MPU9150 are:
    accel/gyro: right-front-up; mag: front-right-down.
    Due to the layout of MPU9150 on the board, there is a 135 degree difference, so a coordinate transformation is needed.
    It is realized by transformation() and transformation_mag() in util.c. These 2 functions are called in ERU_Event_Handler() in MPU9150.c.
    After the transformation, we get identical board coordinate system for accel/gyro/mag: front-left-up.
    CAUTIOUS: acceleration is calculated according to external force!
2016-08-14 GetYaw() but it does not work well due to gyro drift.
    Also it gets yaw angle relative to the heading when power on, rather than course angle.
2016-08-16 Succeeded to get heading angle. Update mag bias.
    1. Get heading angle using only mag data with GetHeading().
    NOTICE that sin() and cos() use radians rather than degrees!!!!!!!
    Remove GetYaw().
    2. Add codes in ERU_Event_Handler(void) in MPU9150.c to calculate mag bias, and update bias in transformation_mag() in util.c.
    The theory is: rotate the board and record the max and min mag value of each axis. Bias is the average of max and min. Print out bias value using serial port, then finally update the bias[3] in util.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
    It is possible to encapsulate mag calibration into a function, but not necessary for now. So far I don't know how to save calibration value to Flash or ROM.
2016-08-16 Apply LPF in GetHeading() to get stable heading.
    Now heading varies within 1 degree when the board is static.
    LPF is not applied near 180/-180 due to data discontinuity, so there is still drastic fluctuation(about 5 degree) between -175 and 175.
2016-08-16 Remove failed code about recording ground pressure and temperature in Initialize().
2016-08-16 If setupDPS() failed(return non-zero value), turn off all 3 state LEDs to inform us.
2016-08-16 Add a counter DPS_ISR_cnt to know how many times DPS_EXT_INT_ISR() has run.
2016-08-16 A trial to change Earth Frame from NWU to NED.
    Details:
    1. change accel/gyro/mag coordinate:
    front-left-up => front-right-down,
    by amending transformation() and transformation_mag() in util.c;
    2. reverse the sign of parameter acc[3] data when calling MadgwickQuaternionUpdate();
    3. change the value of beta to 5 in MadgwickQuaternionUpdate().
2016-08-16 Revert "A trial to change Earth Frame from NWU to NED."
    Revert last commit because after changing Earth Frame, the performance of attitude algorithm is not very good, and honestly I do not fully understand my amendment in last commit...
    When we can better the performance, we will change earth frame to NED for good.
    This reverts commit d761af4e9d95baeb88b77454597c2363b19118ef.
2016-08-28 Creat Buffer struct for InertialNav.
2016-08-28 Creat math lib.
2016-08-28 Create imu to get:
    rotation matrix; imuTransformVectorBodyToEarth();
    position and velocity estimation(basically from AP_InertialNav).
    Now only debug vertical channel, so horizontal-related code is commented out.
2016-08-28 UNcomment function MahonyQuaternionUpdate().
2016-08-28 Prepare to add magnetic declination.
2016-08-28 Change baro-related function names and record time when calc alt.
2016-08-28 Main.c: Add InertialNavUpdate() and test acc_ef, vertical pos/vel with usb output.
2016-08-28 Attitude estimation: change to MahonyQuaternionUpdate().
    Fomerly MadgwickQuaternionUpdate() goes crazy when the board suffers from severe vibration.
2016-08-28 Attitude estimation: change the PI parameters of MahonyQuaternionUpdate() to get better preciser attitude.
2016-08-28 Milestone: vertical InertialNav basically achieved.
    Reset the buffer size to 15;
    Decrease _time_constant_z from 5.0 to 0.5(higher value decreases barometers impact, velocity converges very slowly when this constant is large);
    Change the value subtracted from accel_ef.z(remove influence of gravity) to zero accel_ef.z when put stable. Local gravity is not exactly GRAVITY.
    TODO: _velocity.z still converges slowly if we vibrate the board up and down forcibly for a few seconds. Can we better the performance?
2016-08-30 New Version
    Added DAVE4 Version
2016-08-30 Removed unnecessary files from version control
    Removed unnecessary files from version control
2016-08-30 removed unnecessary folders
2016-08-30 new folder structure
2016-08-31 renamed Dave3 Project
2016-08-31 renamed Dave4 Project
2016-08-31 fixed some float values
2016-09-01 AndroidAPP
2016-09-02 deleted unnecessary folder
2016-09-08 added trimming for yaw-axis in app
